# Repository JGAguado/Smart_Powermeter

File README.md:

[![Documentation Status][documentation-shield]][documentation]
[![GitHub Release][releases-shield]][releases]
[![License][license-shield]](LICENSE)

[![Project Maintenance][maintenance-shield]][maintenance]
[![BuyMeCoffee][buymecoffee-shield]][buymecoffee]

# Smart Powermeter
The Smart Powermeter is powered by a ESP32-S2, allowing the measurement up to 6 CT clamps for reading electric current and real-time display on an 2.9" e-paper display.

Additionally, the 3rd version adds support to voltage measurement with up to 3 voltage measurement channels and independent adjustable gains. 

## Project tree

<li><a href="./Design/">Design</a></li>
<li><a href="./Documentation/">Documentation</a></li>

<li><a href="./README.md">README.md</a></li>

[documentation-shield]: https://readthedocs.org/projects/smart-powermeter/badge/?version=latest&style=for-the-badge
[documentation]: https://smart-powermeter.readthedocs.io/en/latest/

[releases-shield]: https://img.shields.io/github/release/JGAguado/Smart_Powermeter.svg?style=for-the-badge
[releases]: https://github.com/JGAguado/Smart_Powermeter/releases

[license-shield]: https://img.shields.io/badge/License-CC%20BY--NC--SA%204.0-lightgrey.svg?style=for-the-badge

[maintenance-shield]: https://img.shields.io/badge/maintainer-J.%20G.%20Aguado-blue.svg?style=for-the-badge
[maintenance]: https://github.com/JGAguado

[buymecoffee-shield]: https://img.shields.io/badge/buy%20me%20a%20coffee-support-yellow.svg?style=for-the-badge
[buymecoffee]: https://www.buymeacoffee.com/J.G.Aguado

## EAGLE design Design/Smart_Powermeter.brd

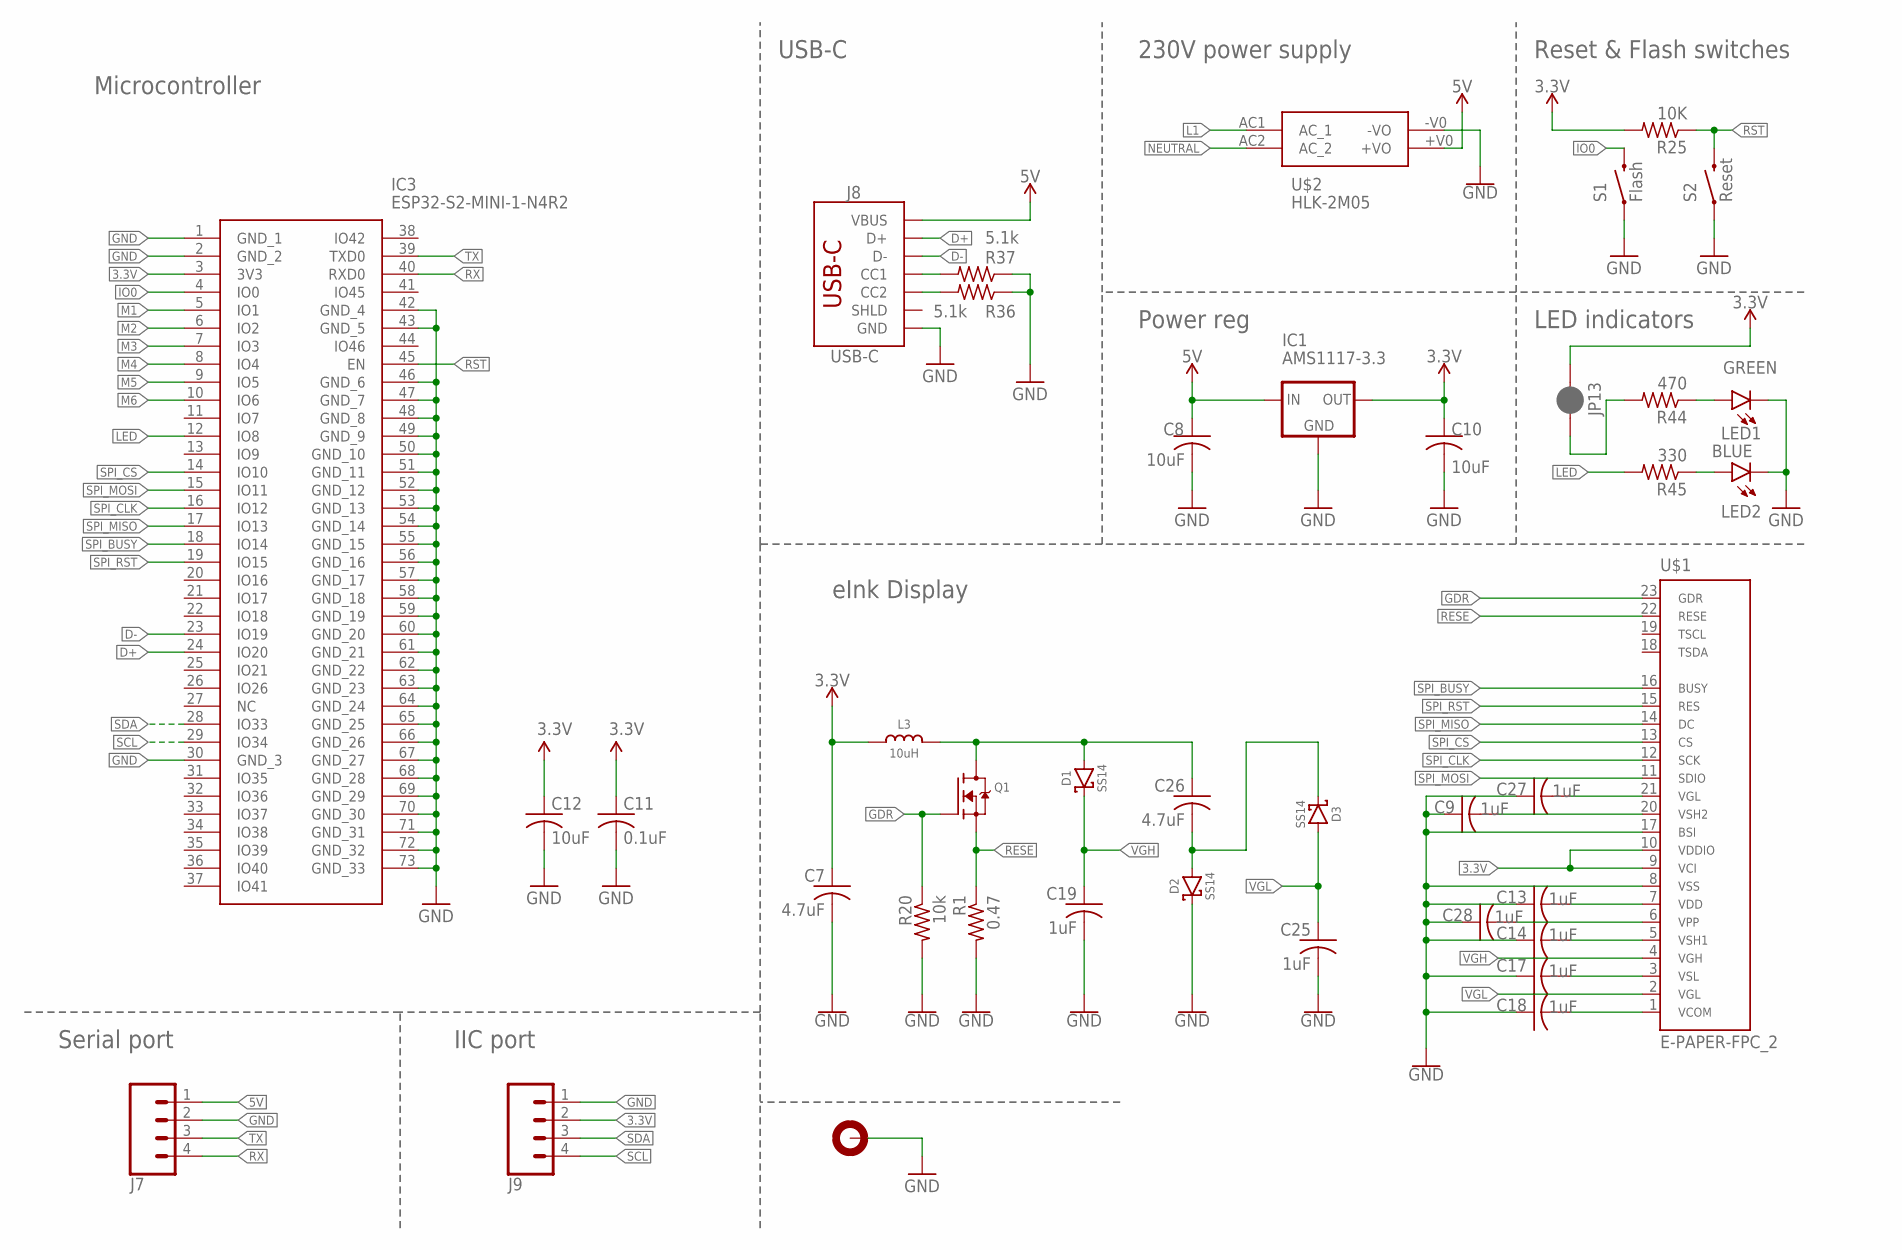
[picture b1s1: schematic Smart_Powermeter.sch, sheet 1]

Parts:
C7, C26: 4.7uF; C0603
C8, C10, C12: 10uF; C0603
C9, C13, C14, C17, C18, C19, C25, C27, C28: 1uF; C0603
C11: 0.1uF; C0603
D1, D2, D3: SS14; SMA-DIODE
H1: 92X84; 92X87
IC1: AMS1117-3.3; SOT223
IC3: ESP32-S2-MINI-1-N4R2; ESP32S2MINI1N4R2
J7, J9: CONN_04PTH; 1X04
J8: USB-C; USB-C-16P-4LAYER-ISOLATED
JP13: JUMPER-SMT_2_NC_PASTE_NO-SILK; SMT-JUMPER_2_NC_PASTE_NO-SILK
L3: 10uH; INDUCTOR_4X4MM_NR401
LED1: GREEN; LED-0603; LCSC C72043
LED2: BLUE; LED-0603
Q1: IRLML0100; SOT23-3
R1: 0.47; R0603
R20: 10k; R0603
R25: 10K; R0603
R36, R37: 5.1k; R0603
R44: 470; R0603
R45: 330; R0603
S1: Flash; TACTILE_SWITCH_SMD_5.2MM
S2: Reset; TACTILE_SWITCH_SMD_5.2MM
U$1: E-PAPER-FPC_2; FPC-05FB-24PH20
U$2: HLK-2M05; LCSC C209909

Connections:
3.3V: C7.1, C10.1, C11.1, C12.1, IC1.2 (OUT), IC3.3 (3V3), J9.2, JP13.1, L3.P$2 (2), R25.2, U$1.9 (16), U$1.10 (15); also elsewhere on the board
5V: C8.1, IC1.3 (IN), J7.1, J8.VBUS1 (VBUS), J8.VBUS2 (VBUS), U$2.+V0 (+VO)
CC3: J8.B5 (CC2), R36.2
CC4: J8.A5 (CC1), R37.2
D+: IC3.24 (IO20), J8.A6 (D+), J8.B6 (D+)
D-: IC3.23 (IO19), J8.A7 (D-), J8.B7 (D-)
GDR: Q1.1 (G), R20.1, U$1.23 (2)
GND: C7.2, C8.2, C9.1, C10.2, C11.2, C12.2, C13.1, C14.1, C17.1, C18.1, C19.2, C25.2, C27.1, C28.1, D2.C, H1.B3,1, H1.B3,2, H1.B3,3, H1.B3,6, H1.P$1, H1.P$2, H1.P$3, H1.P$4, H1.P$5, H1.P$6, H1.P$7, H1.P$8, H1.P$9, H1.P$10, H1.P$11, H1.P$12, H1.P$13, H1.P$14, H1.P$15, H1.P$16, H1.P$17, H1.P$18, H1.P$19, H1.P$20, H1.P$21, H1.P$22, H1.P$23, H1.P$24, H1.P$25, H1.P$26, H1.P$27, H1.P$28, H1.P$29, H1.P$30, H1.P$31, H1.P$32, IC1.1 (GND), IC3.1 (GND_1), IC3.2 (GND_2), IC3.30 (GND_3), IC3.42 (GND_4), IC3.43 (GND_5), IC3.46 (GND_6), IC3.47 (GND_7), IC3.48 (GND_8), IC3.49 (GND_9), IC3.50 (GND_10), IC3.51 (GND_11), IC3.52 (GND_12), IC3.53 (GND_13), IC3.54 (GND_14), IC3.55 (GND_15), IC3.56 (GND_16), IC3.57 (GND_17), IC3.58 (GND_18), IC3.59 (GND_19), IC3.60 (GND_20), IC3.61 (GND_21), IC3.62 (GND_22), IC3.63 (GND_23), IC3.64 (GND_24), IC3.65 (GND_25), IC3.66 (GND_26), IC3.67 (GND_27), IC3.68 (GND_28), IC3.69 (GND_29), IC3.70 (GND_30), IC3.71 (GND_31), IC3.72 (GND_32), IC3.73 (GND_33), J7.2, J8.GND, J8.GND2 (GND), J9.1, LED1.C, LED2.C, R1.2, R20.2, R36.1, R37.1, S1.1, S2.1, U$1.8 (17), U$1.17 (8), U$2.-V0 (-VO); also elsewhere on the board
IO0: IC3.4 (IO0), S1.3 (2)
L1: U$2.AC1 (AC_1); also elsewhere on the board
LED: IC3.12 (IO8), R45.2
M1: IC3.5 (IO1); also elsewhere on the board
M2: IC3.6 (IO2); also elsewhere on the board
M3: IC3.7 (IO3); also elsewhere on the board
M4: IC3.8 (IO4); also elsewhere on the board
M5: IC3.9 (IO5); also elsewhere on the board
M6: IC3.10 (IO6); also elsewhere on the board
unnamed: C9.2, U$1.20 (5)
unnamed: C13.2, U$1.7 (18)
unnamed: C14.2, U$1.5 (20)
unnamed: C17.2, U$1.3 (22)
unnamed: C18.2, U$1.1 (24)
unnamed: C26.2, D2.A, D3.C
unnamed: C26.1, D1.A, L3.P$1 (1), Q1.3 (D)
unnamed: C27.2, U$1.21 (4)
unnamed: C28.2, U$1.6 (19)
unnamed: LED1.A, R44.1
unnamed: JP13.2, R44.2
unnamed: LED2.A, R45.1
NEUTRAL: U$2.AC2 (AC_2); also elsewhere on the board
RESE: Q1.2 (S), R1.1, U$1.22 (3)
RST: IC3.45 (EN), R25.1, S2.3 (2)
RX: IC3.40 (RXD0), J7.4
SCL: IC3.29 (IO34), J9.4
SDA: IC3.28 (IO33), J9.3
SPI_BUSY: IC3.18 (IO14), U$1.16 (9)
SPI_CLK: IC3.16 (IO12), U$1.12 (13)
SPI_CS: IC3.14 (IO10), U$1.13 (12)
SPI_MISO: IC3.17 (IO13), U$1.14 (11)
SPI_MOSI: IC3.15 (IO11), U$1.11 (14)
SPI_RST: IC3.19 (IO15), U$1.15 (10)
TX: IC3.39 (TXD0), J7.3
VGH: C19.1, D1.C, U$1.4 (21)
VGL: C25.1, D3.A, U$1.2 (23)

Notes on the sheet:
Microcontroller
USB-C
Power reg
Reset & Flash switches
Serial port
IIC port
eInk Display
LED indicators
230V power supply

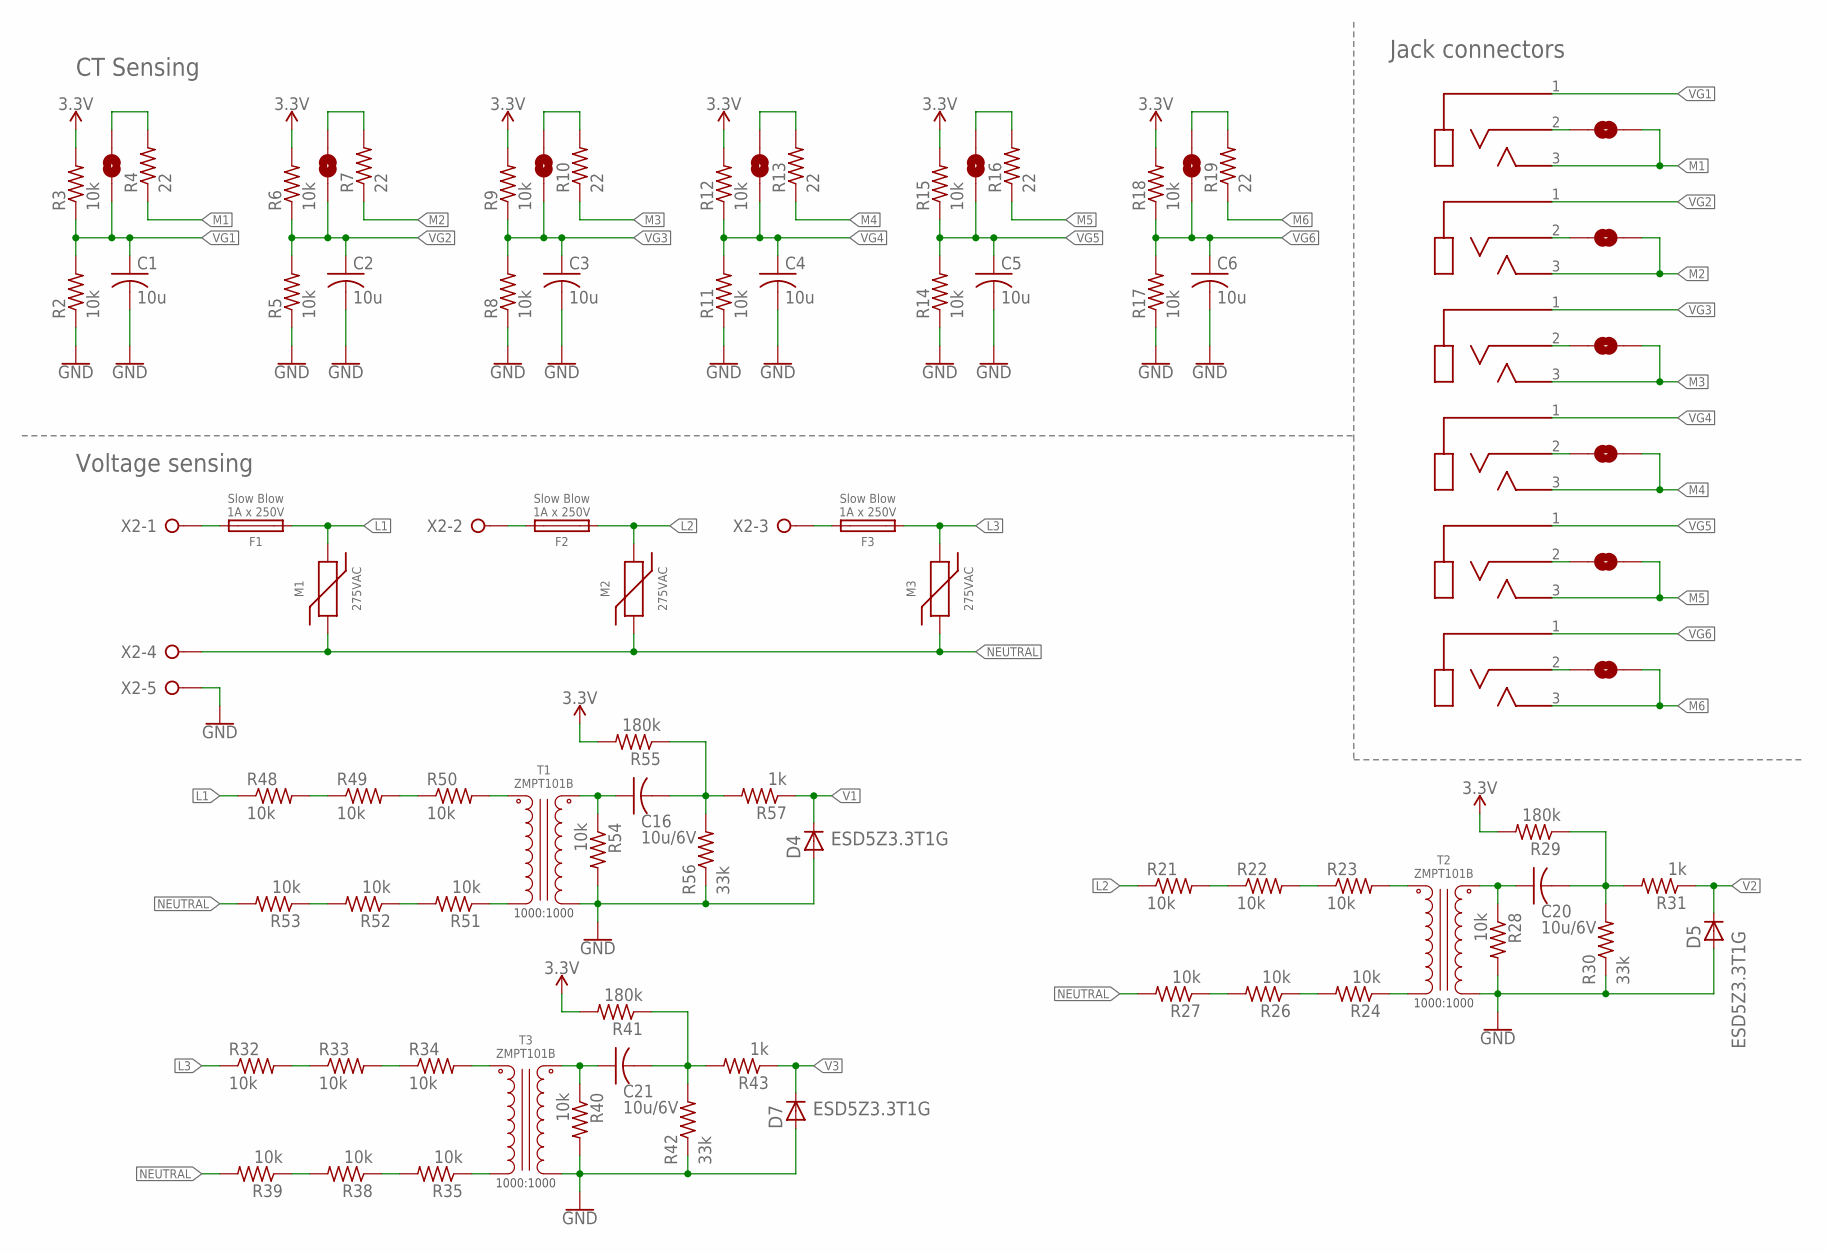
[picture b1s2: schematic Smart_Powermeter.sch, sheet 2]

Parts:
C1, C2, C3, C4, C5, C6: 10u; C0603
C16, C20, C21: 10u/6V; C0603
D4, D5, D7: ESD5Z3.3T1G; SOD-523; LCSC C2827729
F1, F2, F3: 1A x 250V; FUSE; LCSC C340909
J1, J2, J3, J4, J5, J6: AUDIO_JACK_MONO_3.5_3P; HC-PJ-320A-3P-D
JP1, JP2, JP3, JP4, JP5, JP6, JP7, JP8, JP9, JP10, JP11, JP12: JUMPER-SMT_2_NO_NO-SILK; SMT-JUMPER_2_NO_NO-SILK
M1, M2, M3: 275VAC; MOV; LCSC C3260970
R2, R3, R5, R6, R8, R9, R11, R12, R14, R15, R17, R18, R21, R22, R23, R24, R26, R27, R28, R32, R33, R34, R35, R38, R39, R40, R48, R49, R50, R51, R52, R53, R54: 10k; R0603
R4, R7, R10, R13, R16, R19: 22; R0603
R29, R41, R55: 180k; R0603
R30, R42, R56: 33k; R0603
R31, R43, R57: 1k; R0603
T1, T2, T3: ZMPT101B
X2: W237-05P; W237-5P

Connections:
3.3V: R3.2, R6.2, R9.2, R12.2, R15.2, R18.2, R29.2, R41.2, R55.2; also elsewhere on the board
GND: C1.2, C2.2, C3.2, C4.2, C5.2, C6.2, D4.A, D5.A, D7.A, R2.1, R5.1, R8.1, R11.1, R14.1, R17.1, R28.2, R30.1, R40.2, R42.1, R54.2, R56.1, T1.4 (SEC_1), T2.4 (SEC_1), T3.4 (SEC_1), X2.5; also elsewhere on the board
L1: F1.IN (2), M1.1 (2), R48.1; also elsewhere on the board
L2: F2.IN (2), M2.1 (2), R21.1
L3: F3.IN (2), M3.1 (2), R32.1
M1: J1.3, JP8.1, R4.1; also elsewhere on the board
M2: J2.3, JP7.1, R7.1; also elsewhere on the board
M3: J3.3, JP9.1, R10.1; also elsewhere on the board
M4: J4.3, JP10.1, R13.1; also elsewhere on the board
M5: J5.3, JP11.1, R16.1; also elsewhere on the board
M6: J6.3, JP12.1, R19.1; also elsewhere on the board
unnamed: JP1.2, R4.2
unnamed: F1.OUT (1), X2.1
unnamed: F2.OUT (1), X2.2
unnamed: F3.OUT (1), X2.3
unnamed: R21.2, R22.1
unnamed: R22.2, R23.1
unnamed: R24.1, T2.1 (PRI_2)
unnamed: R24.2, R26.1
unnamed: R26.2, R27.1
unnamed: R23.2, T2.2 (PRI_1)
unnamed: C20.1, R28.1, T2.3 (SEC_2)
unnamed: C20.2, R29.1, R30.2, R31.2
unnamed: R32.2, R33.1
unnamed: R33.2, R34.1
unnamed: R35.1, T3.1 (PRI_2)
unnamed: R35.2, R38.1
unnamed: R38.2, R39.1
unnamed: R48.2, R49.1
unnamed: R34.2, T3.2 (PRI_1)
unnamed: C21.1, R40.1, T3.3 (SEC_2)
unnamed: C21.2, R41.1, R42.2, R43.2
unnamed: JP2.2, R7.2
unnamed: JP3.2, R10.2
unnamed: JP4.2, R13.2
unnamed: JP5.2, R16.2
unnamed: JP6.2, R19.2
unnamed: R49.2, R50.1
unnamed: R51.1, T1.1 (PRI_2)
unnamed: R51.2, R52.1
unnamed: R52.2, R53.1
unnamed: R50.2, T1.2 (PRI_1)
unnamed: C16.1, R54.1, T1.3 (SEC_2)
unnamed: C16.2, R55.1, R56.2, R57.2
unnamed: J1.2, JP8.2
unnamed: J2.2, JP7.2
unnamed: J3.2, JP9.2
unnamed: J4.2, JP10.2
unnamed: J5.2, JP11.2
unnamed: J6.2, JP12.2
NEUTRAL: M1.2 (1), M2.2 (1), M3.2 (1), R27.2, R39.2, R53.2, X2.4; also elsewhere on the board
V1: D4.K (C), R57.1
V2: D5.K (C), R31.1
V3: D7.K (C), R43.1
VG1: C1.1, J1.1, JP1.1, R2.2, R3.1
VG2: C2.1, J2.1, JP2.1, R5.2, R6.1
VG3: C3.1, J3.1, JP3.1, R8.2, R9.1
VG4: C4.1, J4.1, JP4.1, R11.2, R12.1
VG5: C5.1, J5.1, JP5.1, R14.2, R15.1
VG6: C6.1, J6.1, JP6.1, R17.2, R18.1

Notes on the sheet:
CT Sensing
Jack connectors
Voltage sensing

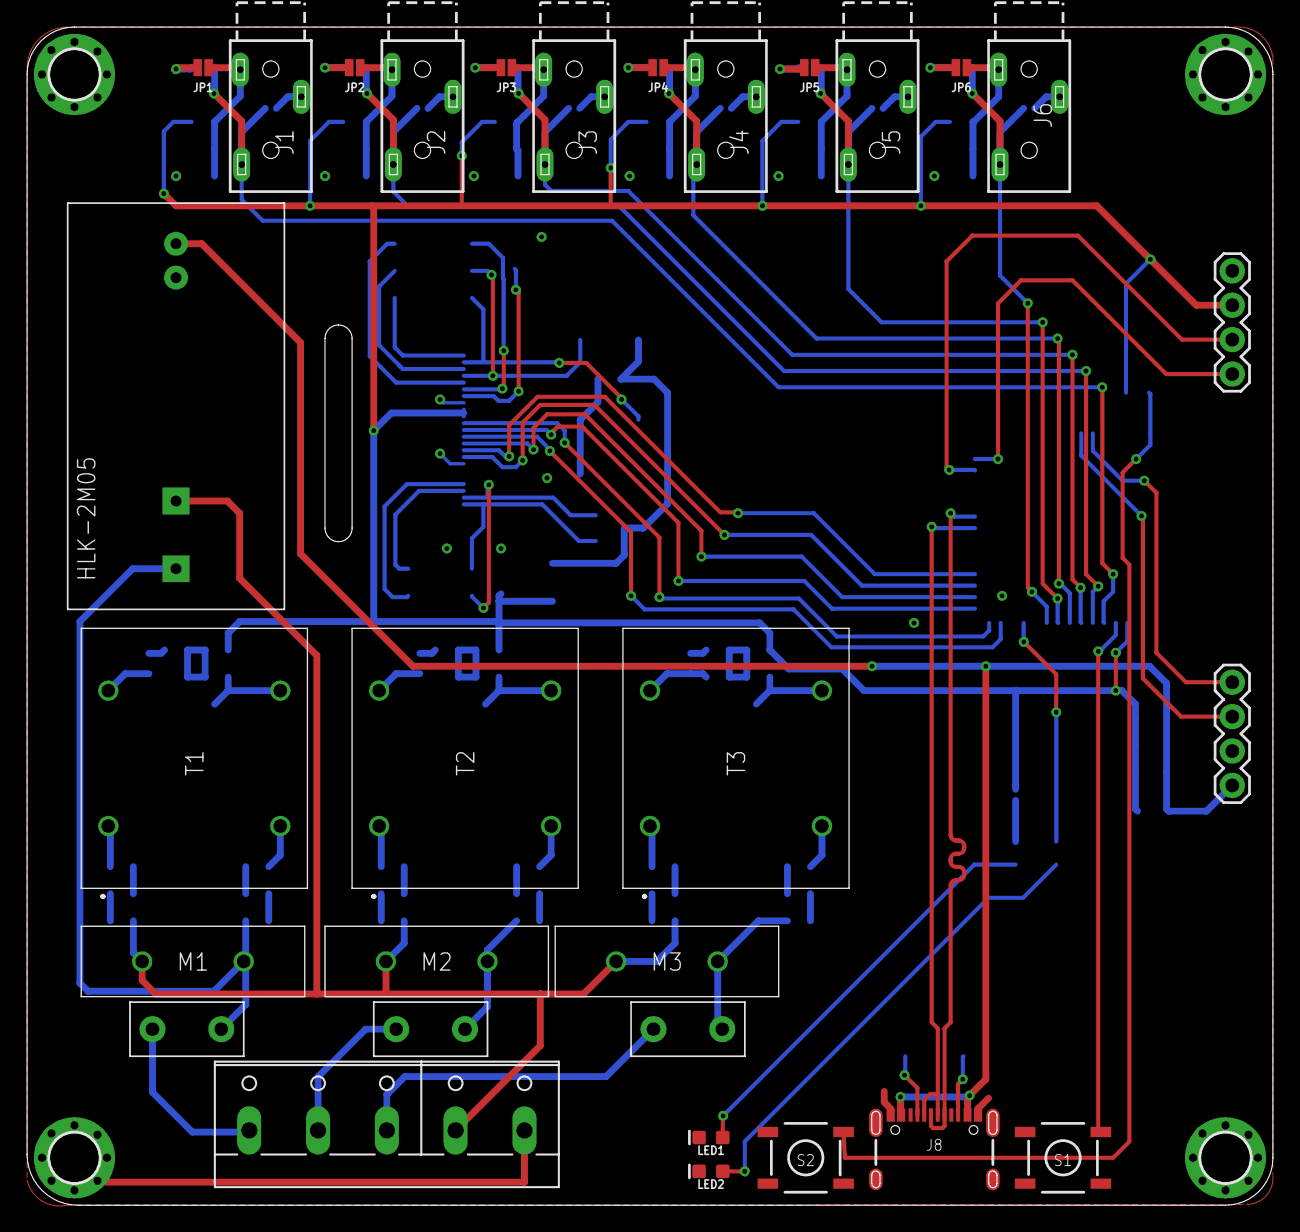
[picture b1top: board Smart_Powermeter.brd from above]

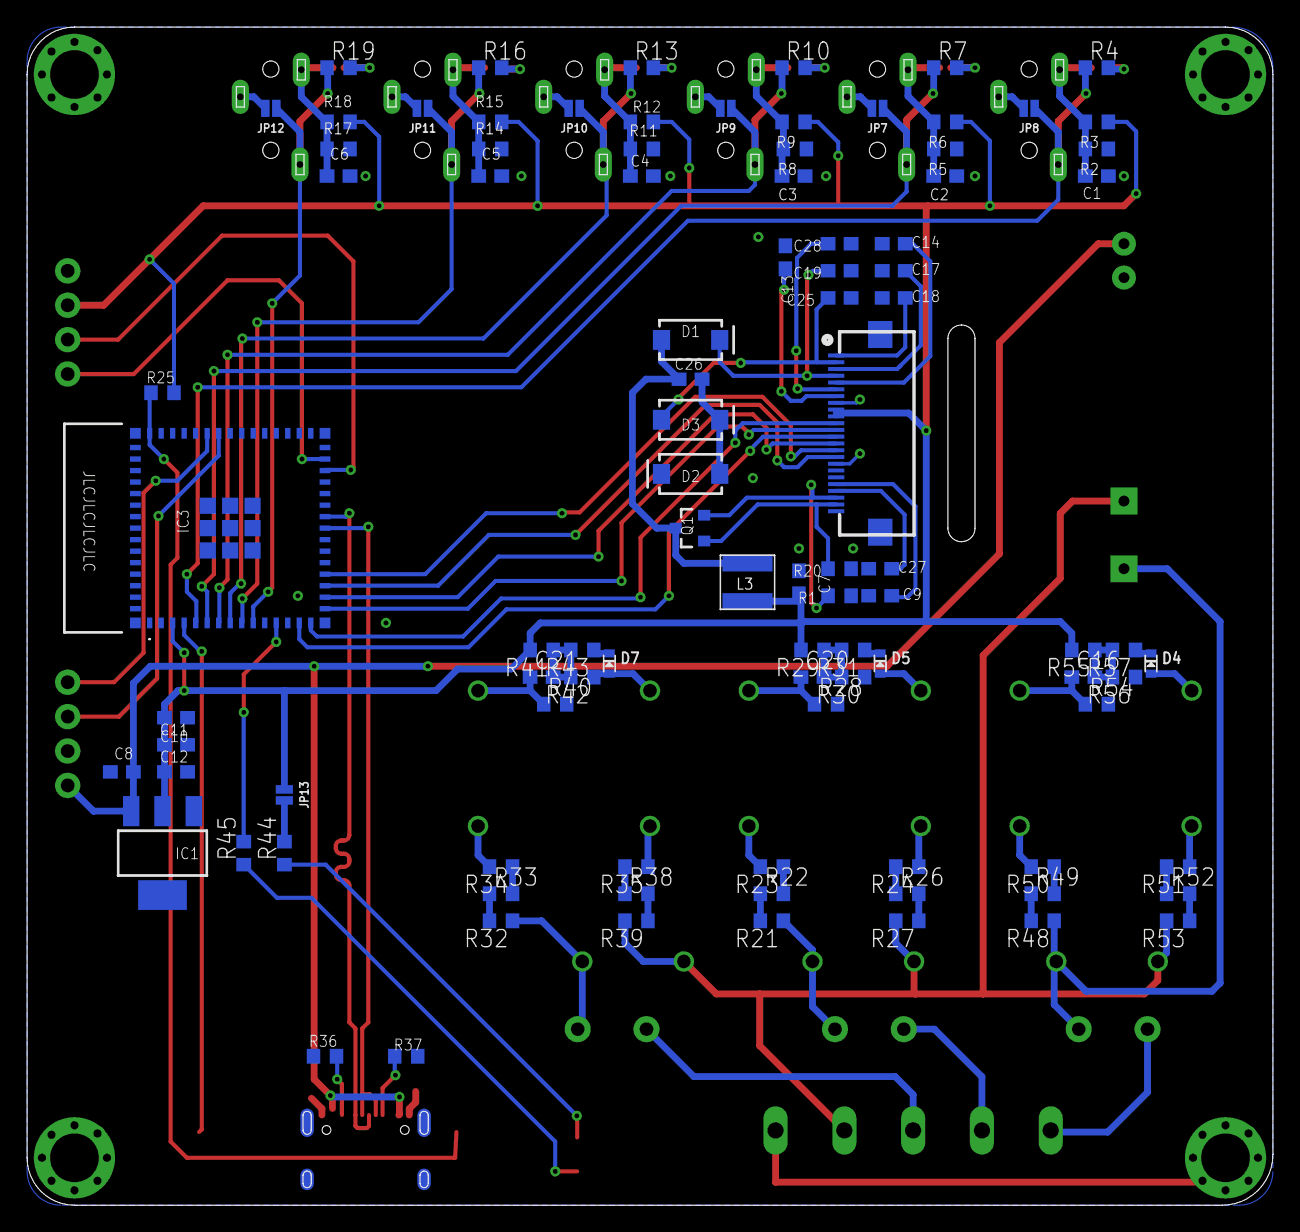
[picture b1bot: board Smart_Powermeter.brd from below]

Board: 2 copper layers, 92.0 x 87.0 mm, 128 parts (97 on the bottom side), 94 nets.

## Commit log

2022-04-13 Added silkscreen design
2022-04-13 Added design files
2022-04-13 Added Documentation
2022-04-13 Updated silkscreen files
2022-04-13 Updated design files fixing Release 1 bugs
2022-04-13 Updated documentation
2022-05-11 Updated documentation with added Datasheet
2022-05-29 Resize dimensions to fit in the 92x87 enclosure
2023-04-19 Added design files of V2
2023-04-19 Added Documentation V3
2023-04-19 docs
2023-04-19 README.md
2023-07-02 updated configuration.yaml
2023-11-14 Updated design files
2024-01-31 fixed the missing "0" on the docs
2024-03-19 First draft for the Pro version
2024-04-03 Updated design files and silkscreen
2024-04-03 Added alternative configuration_1.yaml with: - Web server - MQTT - Input coefficients for linear calibration "a*x + b"
2024-04-19 Documentation
2024-04-22 Removed secrets from configuration.yaml
2024-04-22 removed custom files from configuration.yaml
2024-04-22 Removed custom components from configuration.yaml
2024-05-03 Readme
2024-06-12 Smart Powermeter Pro with V/I measurements directly on the ESP32-S2
2024-06-14 11dB -> 12dB
2024-06-20 fix typos
2024-07-10 Former Eagle files moved to Eagle
2024-07-10 Added KiCad files with a first draft for the V3R1
2024-08-01 First draft V3R1
2024-08-06 Cleared path around antenna and removed Serial port
2025-03-03 Update configuration.yaml to work with >= ESPHome 2025.2.0
    https://esphome.io/changelog/2025.2.0.html#image-components
    "the type configuration variable is now mandatory"
2025-05-04 Add GA support

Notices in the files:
parts and their libraries:
SparkFun-Connectors: Licensing: Creative Commons ShareAlike 4.0 International - https://creativecommons.org/licenses/by-sa/4.0
microbuilder: This work is placed in the public domain, and may be freely used for commercial and non-commercial work with the following conditions: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
